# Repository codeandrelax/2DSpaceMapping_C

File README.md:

# 2DSpaceMapping autonomous vehicle 🚗 ➡️ HARDWARE SIDE

This is a hardware_branch which contains models for assembly electronic devices/ modules / components. <br />
For more detailed informations about each used modul, visit Wiki 📜 page. <br />
 <br />
## Currently implemented :
  - edge connector
  - MCU PIC24FJ64GA002-I/SP
  - normally opened button TS02-66-50-BK-100-SCR-D
  - WiFi module WRL-17146
  - Slide-Switch SLW-883935-2A-D
  - 2x4 pin socket for WiFi module 5-534206-4
  - MCU socket 1-2199298-9

## Guidance through file hierarchy :
  - Symbols_footprints ➡️ contains .kicad_sym & .kicad_mod files for each used modul/ component on the scheme
  - pcb ➡️  contains .png screenshots of .kicad_pcb file
  - schema ➡️  contains .png screenshots of .kicad_sch file and .pdf file exported from KiCad project
  - work ➡️  project work directory. Run ♻️ the pcb_layout_c.kicad_pro form this dir using KiCad7.0 or latest. <br /> (KiCad DOWNLOAD link 🆓⬇️ : https://www.kicad.org/download/windows/)
  - components.csv ➡️ list of used components for this project with Mouser Electronics link to each of them. <br /> (https://hr.mouser.com/?gad_source=1&gclid=Cj0KCQiAw6yuBhDrARIsACf94RVZDfmztJkKG18F4qrYKF0iiaaEyd-j5r4cXpUXJpGI24s9JXtPty4aAuFKEALw_wcB)

## KiCad Schema : 

## KiCad PCB Layout: 

## KiCad 3D View PCB :

## Guidance through Git Bash commands :
1. 		git checkout hardware_branch
2. 		git pull origin hardware_branch
3. 🚧 ...modification... 🚧
4. 		git add .
5. 		git commit -m "Issue#n
   		- Line1
   		- Line2
   		- ..."
     n  - the number of Issue being worked on
7. 		git push origin hardware_branch

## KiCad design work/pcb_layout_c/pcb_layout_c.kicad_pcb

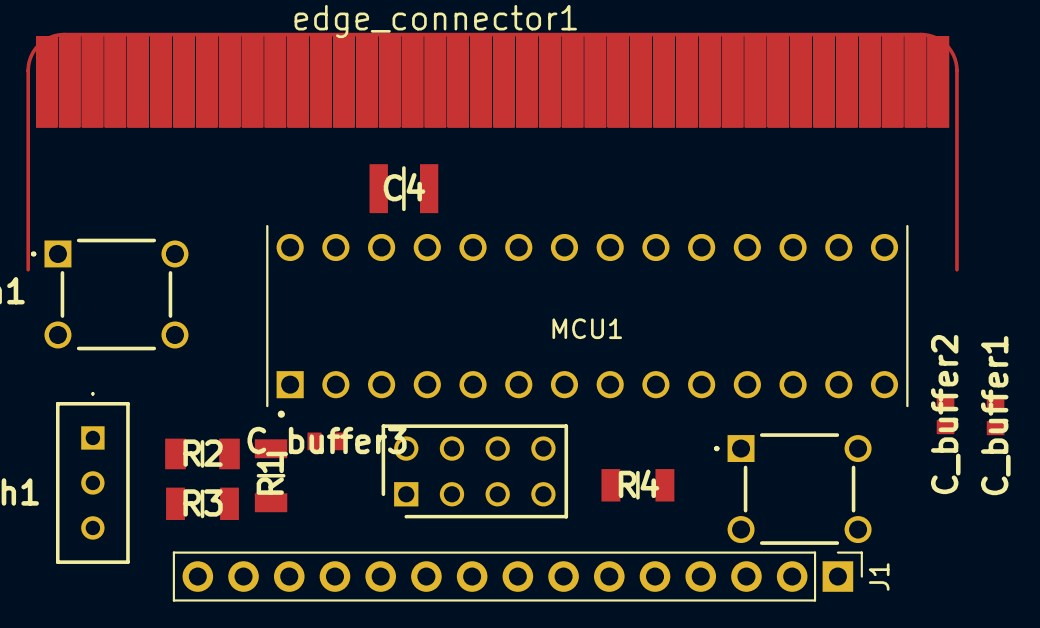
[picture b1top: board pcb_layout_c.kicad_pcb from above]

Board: 2 copper layers, 15 parts (0 on the bottom side), 22 nets, no tracks yet.

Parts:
C4: 10uF; CAPC3225X210N
C_buffer1, C_buffer2, C_buffer3: 0.1uF; CAPC1608X95N
J1: Conn_01x15_Pin; PinHeader_1x15_P2.54mm_Vertical
MCU1: 2024-01-28_16-23-25_PIC24FJ64GA002-X_SP; DIP762W60P254L3556H510Q28
MCU_reset_button1: TS02-66-50-BK-100-SCR-D; TS026650BK100SCRD
MCU_slide_switch1: SLW-883935-2A-D; SLW8839352AD
R1, R3, R4: 10K; RESC3216X60N
R2: 250; RESC3216X70N
WiFi_reset_button1: TS02-66-50-BK-100-SCR-D; TS026650BK100SCRD
WiFi_socket1: 5-534206-4; RHDR8W69P254_2X4_1016X503X877P
edge_connector1: edge_connector1; BBC_EDGE

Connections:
BAT_CONN: J1.10, MCU1.2 (AN0/VREF+/CN2/RA0)
GND: C4.2, C_buffer1.1, C_buffer2.2, C_buffer3.2, J1.3, J1.11, MCU1.8 (VSS), MCU1.27 (VSS), MCU_reset_button1.1 (NO_1), MCU_reset_button1.2 (NO_2), WiFi_reset_button1.1 (NO_1), WiFi_reset_button1.2 (NO_2), WiFi_socket1.1, WiFi_socket1.3, WiFi_socket1.5, edge_connector1.P$35 (EDGE_GND_1), edge_connector1.P$36 (EDGE_GND_2), edge_connector1.P$37 (EDGE_GND_3), edge_connector1.P$38 (EDGE_GND_4), edge_connector1.P$39 (EDGE_GND_5), edge_connector1.P$40 (EDGE_GND_16), edge_connector1.P$75 (EDGE_GND_1), edge_connector1.P$76 (EDGE_GND_2), edge_connector1.P$77 (EDGE_GND_3), edge_connector1.P$78 (EDGE_GND_4), edge_connector1.P$79 (EDGE_GND_5), edge_connector1.P$80 (EDGE_GND_16)
MCLR: J1.14, MCU_slide_switch1.3 (NO), R3.1
unnamed: C_buffer3.1, R1.1, R2.1
unnamed: MCU1.1 (*MCLR), MCU_slide_switch1.2 (COM)
unnamed: MCU1.17 (TCK/RP8/SCL1/CN22/PMD4/RB8), edge_connector1.P$33 (EDGE_P19), edge_connector1.P$73 (EDGE_P19)
unnamed: MCU1.18 (TDO/RP9/SDA1/CN21/PMD3/RB9), edge_connector1.P$34 (EDGE_P20), edge_connector1.P$74 (EDGE_P20)
unnamed: C4.1, MCU1.20 (VCAP/VDDCORE)
unnamed: MCU_reset_button1.3 (COM_1), MCU_reset_button1.4 (COM_2), R2.2
unnamed: R4.2, WiFi_reset_button1.3 (COM_1), WiFi_reset_button1.4 (COM_2), WiFi_socket1.6
PGC1: J1.13, MCU1.5 (PGC1/EMUC1/AN3/C2IN+/RP1/CN5/RB1)
PGD1: J1.12, MCU1.4 (PGD1/EMUD1/AN2/C2IN-/RP0/CN4/RB0)
RX: J1.1, MCU1.15 (PGC3/EMUC3/RP6/ASCL1/CN24/PMD6/RB6)
RX input: MCU1.21 (PGD2/EMUD2/TDI/RP10/CN16/PMD2/RB10), WiFi_socket1.7
SCL2: J1.9, MCU1.7 (AN5/C1IN+/RP3/SCL2/CN7/RB3)
SDA2: J1.8, MCU1.6 (AN4/C1IN-/RP2/SDA2/CN6/RB2)
SPI1 Clock Output: J1.6, MCU1.24 (AN11/RP13/CN13/PMRD/RB13)
SPI1 Data Output: J1.7, MCU1.25 (AN10/CVREF/RTCC/RP14/CN12/PMWR/RB14)
SPI1 Slave Select Output: J1.5, MCU1.23 (AN12/RP12/CN14/PMD0/RB12)
TX: J1.2, MCU1.16 (RP7/INT0/CN23/PMD5/RB7)
TX out: MCU1.26 (AN9/RP15/CN11/PMCS1/RB15), WiFi_socket1.2
VDD: C_buffer1.2, C_buffer2.1, J1.4, J1.15, MCU1.13 (VDD), MCU1.28 (VDD), R1.2, R3.2, R4.1, WiFi_socket1.4, WiFi_socket1.8, edge_connector1.P$27 (EDGE_3V3_1), edge_connector1.P$28 (EDGE_3V3_2), edge_connector1.P$29 (EDGE_3V3_3), edge_connector1.P$30 (EDGE_3V3_4), edge_connector1.P$31 (EDGE_3V3_5), edge_connector1.P$32 (EDGE_3V3_6), edge_connector1.P$67 (EDGE_3V3_1), edge_connector1.P$68 (EDGE_3V3_2), edge_connector1.P$69 (EDGE_3V3_3), edge_connector1.P$70 (EDGE_3V3_4), edge_connector1.P$71 (EDGE_3V3_5), edge_connector1.P$72 (EDGE_3V3_6)

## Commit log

2024-01-24 Deleted unnecessary files
2024-01-24 File reorganization
2024-01-25 Added questions for second sprint
2024-01-26 Issue#6 & Issue#9 Added footprint and symbol for edge connector Added footprint and symbol for microcontroller
2024-01-30 Added csv file and other minor files
2024-02-08 Added hierarchy of folders - Added folders for symbols and footprints - Added symbols and footprints for components used
2024-02-08 Added working directory - Added KiCad project
2024-02-13 Issue #21 & Issue #23 Create KiCad schematic Update Symbol_Footprint directory
2024-02-13 Issue #25 : Dodavanje .png fajlova sa prikazom seme cjelokupnog sistema
2024-02-13 Issue #23 : Azuriranje Symbol_footprint direktorijuma
2024-02-13 Issue #22 : Kreiranje PCB dizajna cjelokupnog sistema
2024-02-13 Issue #26 : Dodavanje .png fajlova sa prikazom pcb-a
2024-02-13 Issue #25 : Dodavanje .png fajlova sa prikazom seme cjelokupnog sistema Dodavanje .pdf fajla sa prikazom seme
2024-02-13 Issue # 25 : Dodavanje .png fajlova sa prikazom seme cjelokupnog sistema
2024-02-14 Issue #24 : Kreiranje sumarne dokumentacije cjelokupnog sistema Dodan sumarni .pdf fajl sa vizuelnim prikazom kicad seme, pcb layout-a i 3d prikaza plocice
2024-02-23 Issue #27 : Promjena velicine sheeta na KiCad schemi Promijenjana velicina okvira na .kicad_sch fajlu
2024-04-16 Issue #35 : Provjeravanje ispravnosti mikrokontrolera Dodan .c fajl kao testni primjerak za provjeru ispravnosti MCU
2024-04-17 Issue #36: Provjera ispravnosti PCB pločice Dodane fotografije izmjerenih napona na postojećoj Joy-Car pločici i na izrađenoj PCB pločici
2024-04-17 Issue #37: Osposobljavanje UART-a za komunikaciju sa Wi-Fi modulom
2024-04-21 Issue #31 : Pokretanje tockova auta Dodan .c fajl sa kodom za pokretanje tockova vozila u svim pravcima
2024-04-23 Issue #33 : Pokretanje servo motora Dodan .c fajl sa izvornim kodom za pokretanje servo motora u 3 tacke
2024-04-24 Issue #33: Pokretanje servo motora Napisan c fajl za pokretanje servo motora u 5 razlicitih pozicija
2024-04-24 Issue #32: Pokretanje senzora za distancu Napisan c fajl za pokretanje senzora za distancu. Kada predmet pridje na 10cm, upali se LE dioda
2024-04-24 Issue #33 : Pokretanje servo motora
2024-04-24 Issue #32 : Pokretanje senzora za distancu
2024-04-24 Issue #31 : Pokretanje tockova auta
2024-05-10 Issue #39: Testiranje kretanja auta uz pomoc senzora Napisan C kod za kretanje auta i izbjegavanje prepreka. Kod je potrebno optimizovati
2024-05-14 Issue #39: Testiranje kretanja auta uz pomoc senzora Napisan C kod za kretanje auta i izbjegavanje prepreka. Kod je potrebno dodatno optimizovati
2024-05-14 Issue #28: Kreiranje GUI aplikacije
2024-05-14 Added wifi module test files for pc side (wifi.py) and microcontroller side(wifi.c)
2024-05-15 Issue #39: Testiranje kretanja auta uz pomoc senzora Napisan C kod za kretanje auta i izbjegavanje prepreka. Finalna verzija koda
2024-05-17 Dodavanje demo videa
